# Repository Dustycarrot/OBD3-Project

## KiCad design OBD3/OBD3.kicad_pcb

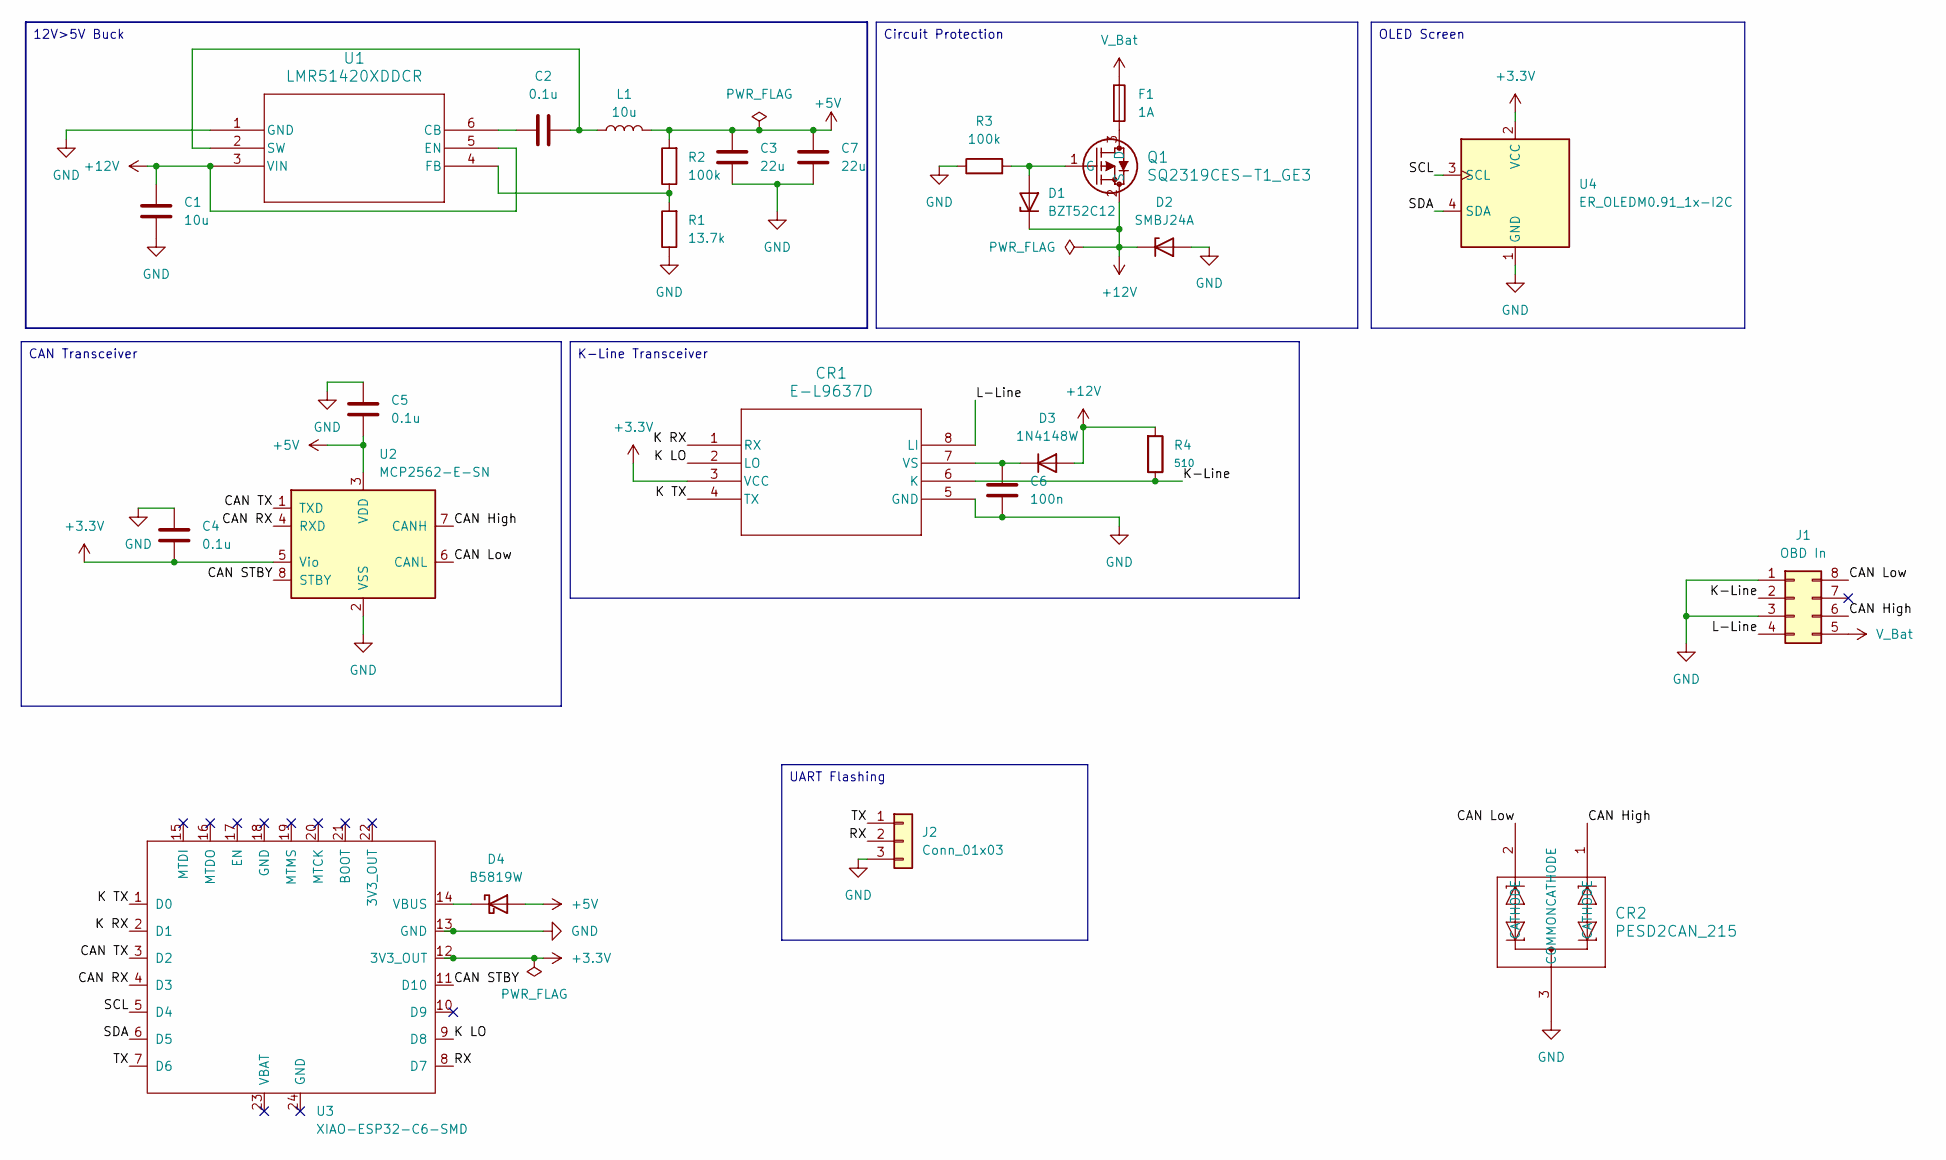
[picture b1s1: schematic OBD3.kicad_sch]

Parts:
C1: 10u; L_1206_3216Metric_Pad1.22x1.90mm_HandSolder
C2, C4, C5: 0.1u; C_0603_1608Metric_Pad1.08x0.95mm_HandSolder
C3, C7: 22u; L_1206_3216Metric_Pad1.22x1.90mm_HandSolder
C6: 100n; C_0603_1608Metric_Pad1.08x0.95mm_HandSolder
CR1: E-L9637D; SO-8_3.9x4.9mm_P1.27mm
CR2: PESD2CAN_215; SOT23_TO-236AB_NEX
D1: BZT52C12; Nexperia_CFP3_SOD-123W
D2: SMBJ24A; DIOM5436X261N
D3: 1N4148W; D_SOD-123
D4: B5819W; SDO_SOD-123_MCC
F1: 1A; LED_1206_3216Metric_Pad1.42x1.75mm_HandSolder
J1: OBD In; PinSocket_2x04_P2.54mm_Vertical
J2: Conn_01x03; PinHeader_1x03_P2.54mm_Vertical
L1: 10u; IND_BOURNS_SRR6028
Q1: SQ2319CES-T1_GE3; PMOSGSD_SOT-23_TO-236_VIS
R1: 13.7k; C_0603_1608Metric_Pad1.08x0.95mm_HandSolder
R2, R3: 100k; C_0603_1608Metric_Pad1.08x0.95mm_HandSolder
R4: 510; R_1210_3225Metric_Pad1.30x2.65mm_HandSolder
U1: LMR51420XDDCR; SOT-23-6_Handsoldering
U2: MCP2562-E-SN; SOIC-8_3.9x4.9mm_P1.27mm
U3: XIAO-ESP32-C6-SMD; XIAO-ESP32-C6-SMD NO BOTPADS
U4: ER_OLEDM0.91_1x-I2C; PinHeader_1x04_P2.54mm_Vertical

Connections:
+3.3V: C4.2, CR1.3 (VCC), U2.5 (Vio), U3.12 (3V3_OUT), U4.2 (VCC)
+5V: C3.2, C5.2, C7.2, D4.2 (A), L1.2, R2.2, U2.3 (VDD)
+12V: C1.2, D1.1 (K), D2.1 (K), D3.2 (A), Q1.2 (S), R4.1, U1.3 (VIN), U1.5 (EN)
/CAN High: CR2.1 (CATHODE), J1.6, U2.7 (CANH)
/CAN Low: CR2.2 (CATHODE), J1.8, U2.6 (CANL)
/CAN RX: U2.4 (RXD), U3.4 (D3)
/CAN STBY: U2.8 (STBY), U3.11 (D10)
/CAN TX: U2.1 (TXD), U3.3 (D2)
/K LO: CR1.2 (LO), U3.9 (D8)
/K RX: CR1.1 (RX), U3.2 (D1)
/K TX: CR1.4 (TX), U3.1 (D0)
/K-Line: CR1.6 (K), J1.2, R4.2
/L-Line: CR1.8 (LI), J1.4
/RX: J2.2, U3.8 (D7)
/SCL: U3.5 (D4), U4.3 (SCL)
/SDA: U3.6 (D5), U4.4 (SDA)
/TX: J2.1, U3.7 (D6)
GND: C1.1, C3.1, C4.1, C5.1, C6.2, C7.1, CR1.5 (GND), CR2.3 (COMMONCATHODE), D2.2 (A), J1.1, J1.3, J2.3, R1.1, R3.1, U1.1 (GND), U2.2 (VSS), U3.13 (GND), U4.1 (GND)
unnamed: C6.1, CR1.7 (VS), D3.1 (K)
unnamed: D1.2 (A), Q1.1 (G), R3.2
unnamed: D4.1 (K), U3.14 (VBUS)
unnamed: F1.2, Q1.3 (D)
unnamed: C2.1, U1.6 (CB)
unnamed: R1.2, R2.1, U1.4 (FB)
unnamed: C2.2, L1.1, U1.2 (SW)
V_Bat: F1.1, J1.5

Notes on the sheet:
CAN Transceiver
Circuit Protection
K-Line Transceiver
OLED Screen
UART Flashing
12V>5V Buck

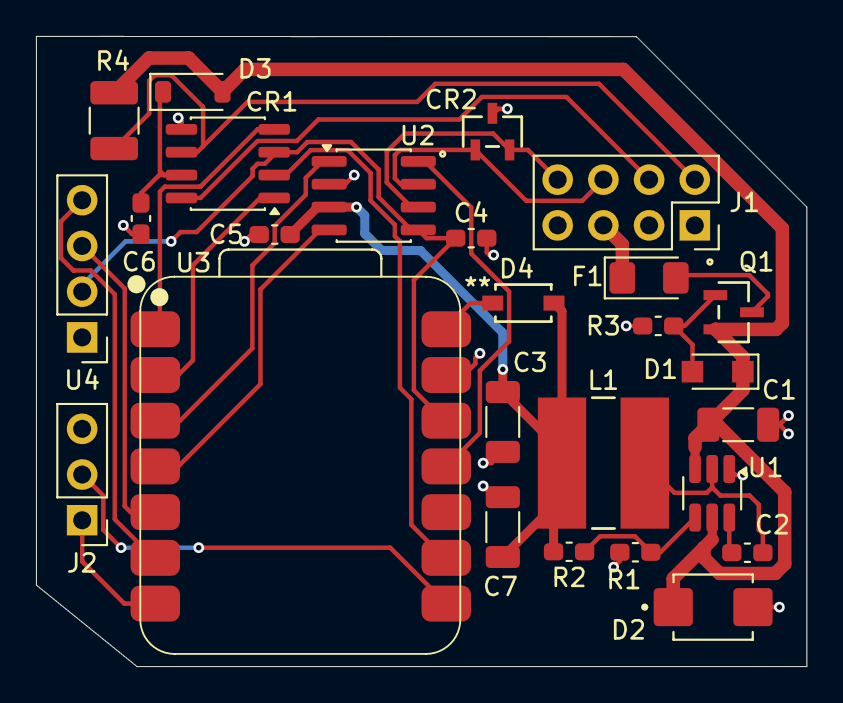
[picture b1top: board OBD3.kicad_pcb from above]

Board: 2 copper layers, 42.8 x 35.0 mm, 26 parts (0 on the bottom side), 26 nets.
